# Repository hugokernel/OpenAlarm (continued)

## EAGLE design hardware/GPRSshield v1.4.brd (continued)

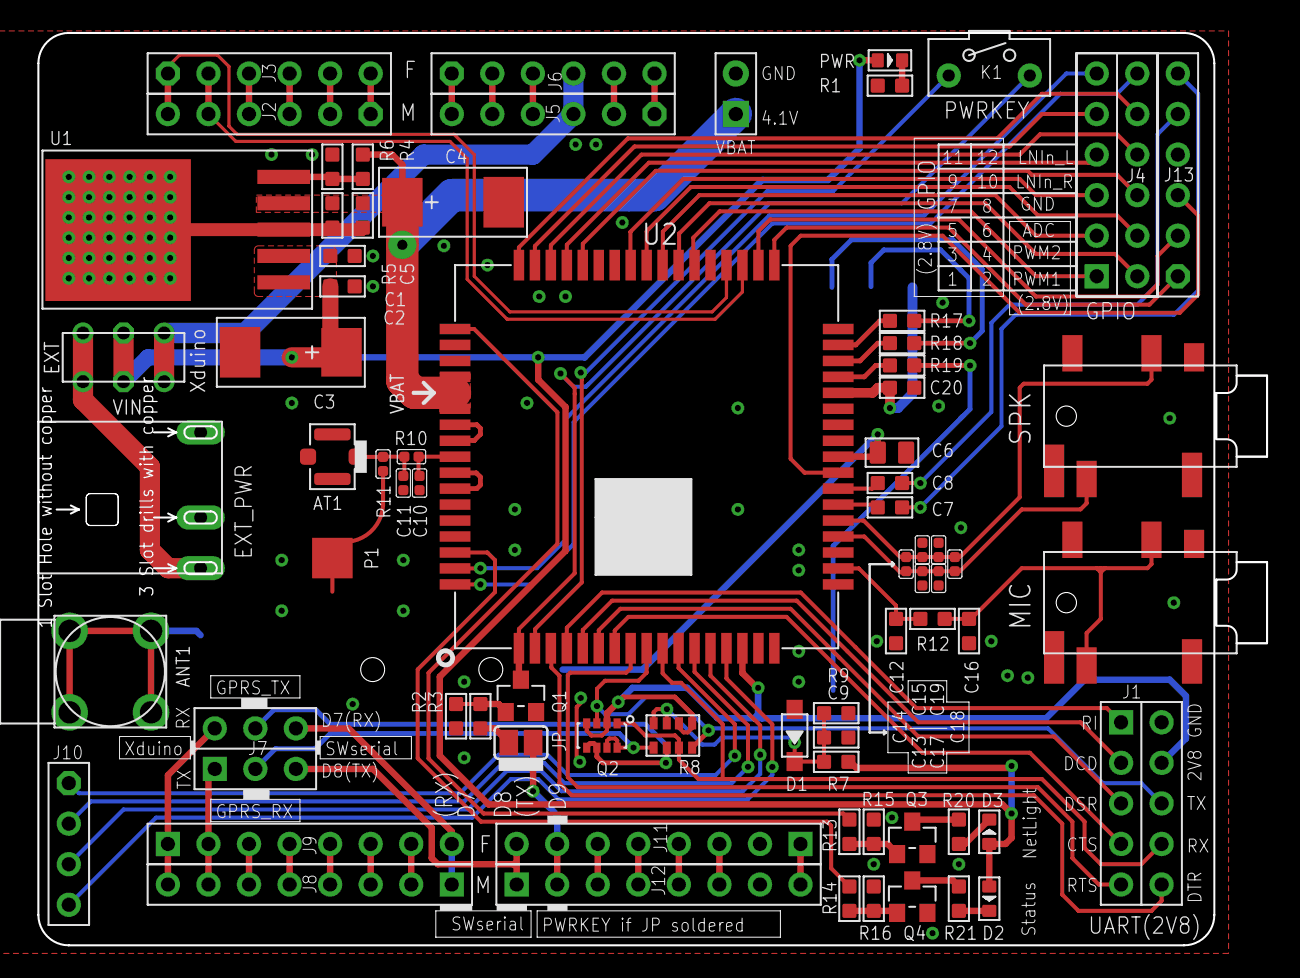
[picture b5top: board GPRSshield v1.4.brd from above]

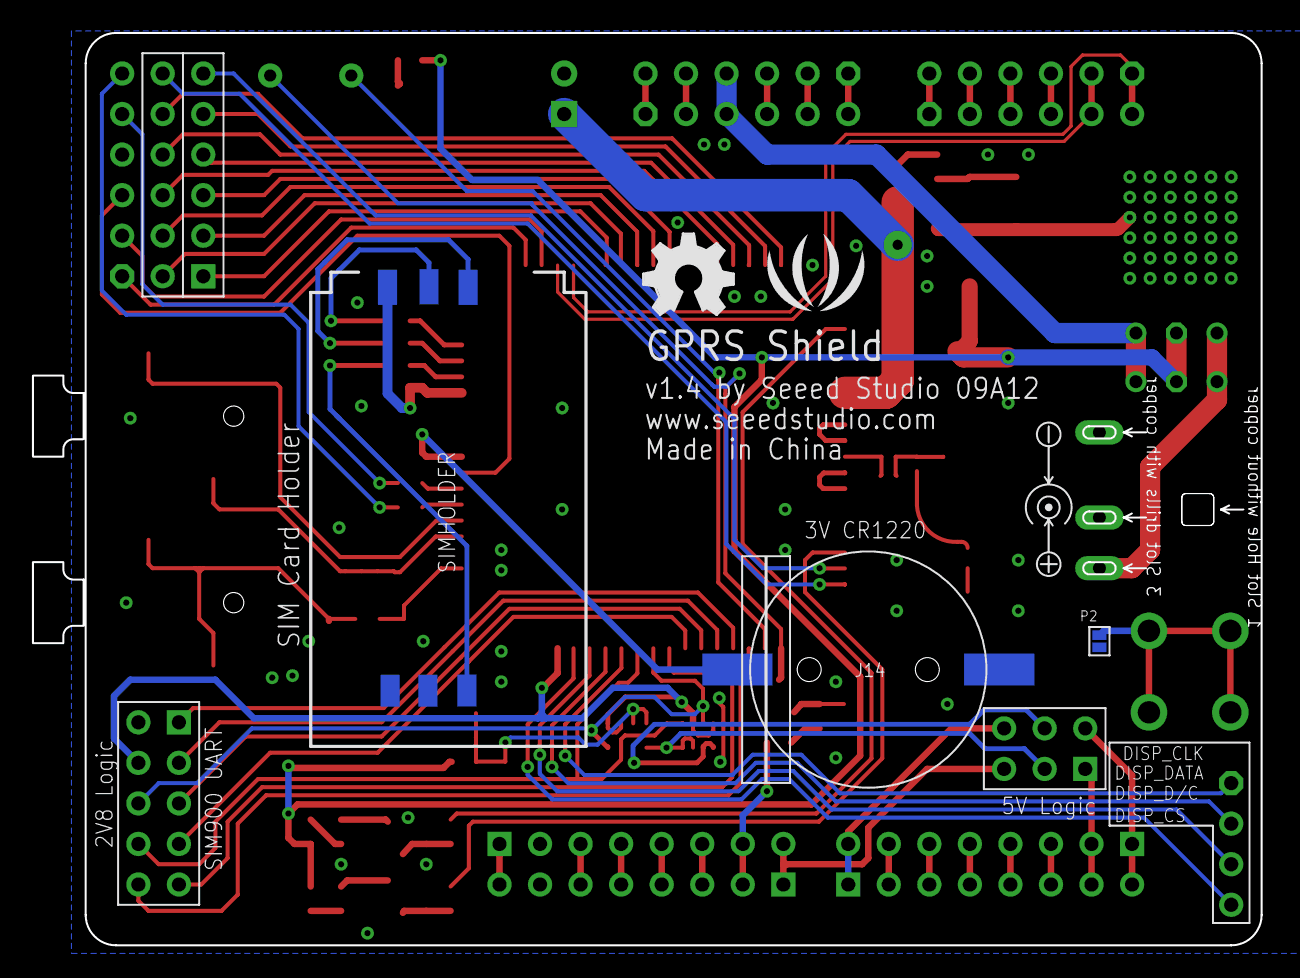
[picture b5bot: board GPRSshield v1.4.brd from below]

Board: 2 copper layers, 77.0 x 57.1 mm, 79 parts (6 on the bottom side), 94 nets.

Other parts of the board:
LOGO1: LOGO-SEEEDSTUDIO-SILK; LOGO_SILK
LOGO2: LOGO-OSHW-FILLX0200-NT; OSHW_FILLX200_NOTEXT

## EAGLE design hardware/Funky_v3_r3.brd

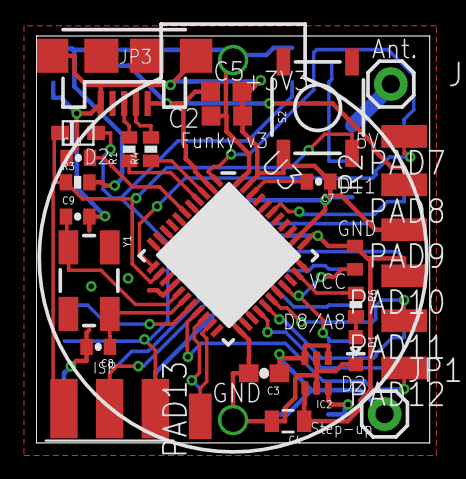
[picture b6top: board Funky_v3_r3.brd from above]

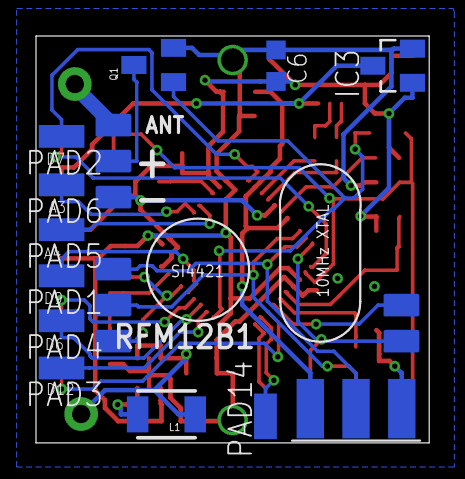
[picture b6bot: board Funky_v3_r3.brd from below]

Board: 2 copper layers, 21.8 x 22.6 mm, 43 parts (12 on the bottom side), 35 nets.

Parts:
BAT2: BATTCOM_20MM_PTH
C2: 100nF; C0603K
C3: 1µ; 0603-CAP
C4: 10µ; 0805
C5: 1uF; C0603K
C6: 1u; C0603K
C7: 100nF; 0402-CAP
C8, C9: 22pF; 0402-CAP
C10: 1uF; 0402-CAP
D1: Green; LED-0603
D2: SOD-323F
IC2: LTC3525; SC70
IC3: MCP1703CB; SOT23
JP1, JP2: M01PTH; 1X01
JP3: USB-MICROB
L1: 10 µH; 1210
PAD1, PAD2, PAD3, PAD4, PAD5, PAD6, PAD7, PAD8, PAD9, PAD10, PAD11, PAD12, PAD13, PAD14: SMD1,27-2,54
Q1: P-MOSFET; SOT23
R1, R4: 22; 0402-RES
R2: 100K; R0402
R3: 10K; 0402-RES
R6: 330; 0402-RES
RFM12B1: RFM12B_MINPADS; RFM12B-MINPADS
S2: !RESET; TACTILE_SWITCH_SMD
U3: ATMEGA32U4; QFN-44-NOPAD
U$2: AVR-ISP-6-EDGE; 6PAD_ISP
Y1: 8MHz; CRYSTAL-SMD-5X3

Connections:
A3: PAD6.1, U3.39
A4: PAD5.1, U3.40
AREF: C7.2, U3.42
D2: PAD12.1, U3.19
D3: RFM12B1.IRQ, U3.18
D4: D2.A, Q1.1, U3.25
D6: PAD4.1, U3.27
D7: PAD2.1, U3.1
D8: PAD11.1, U3.28
D9: PAD1.1, U3.29
D10: R2.1, RFM12B1.SEL, U3.30
D11: PAD7.1, U3.12
D12: PAD3.1, U3.26
D13: R6.1, U3.32
D+: JP3.D+, R1.2
D-: JP3.D-, R4.2
GND: BAT2.2, C2.2, C3.2, C4.2, C5.2, C6.2, C7.1, C8.2, C9.2, C10.1, D1.C, IC2.2, IC2.5, IC3.1, JP3.GND, JP3.MT1, JP3.MT2, PAD9.1, RFM12B1.GND, S2.1, U3.5, U3.15, U3.23, U3.33, U3.35, U3.43, U$2.GND
MISO: RFM12B1.SDO, U3.11, U$2.MISO
MOSI: RFM12B1.SDI, U3.10, U$2.MOSI
unnamed: C9.1, U3.16, Y1.1
unnamed: R1.1, U3.4
unnamed: JP2.1, RFM12B1.ANT
unnamed: C8.1, U3.17, Y1.3
unnamed: C10.2, U3.6
unnamed: D1.A, R6.2
unnamed: R4.1, U3.3
unnamed: Q1.3, RFM12B1.VDD
unnamed: IC2.6, L1.2
RESET: D2.C, R3.1, S2.3, U3.13, U$2.RST
RXI: PAD14.1, U3.20
SCK: RFM12B1.SCK, U3.9, U$2.SCK
TXO: PAD13.1, U3.21
VBUS: C5.1, IC3.3, JP3.VBUS, PAD8.1, U3.2, U3.7, U$2.VCC
VCC: BAT2.1, C2.1, C4.1, C6.1, IC2.4, IC3.2, PAD10.1, Q1.2, R2.2, R3.2, U3.14, U3.24, U3.34, U3.44
VIN: C3.1, IC2.1, IC2.3, JP1.1, L1.1

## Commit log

2014-01-17 Doc + Funky v3
2015-06-10 Node version 1.0.0
2015-08-03 Hardware update
    Node 1.0.0, export and node shield
2015-08-03 Documentation uploaded
2015-08-03 Gitignore update
2015-08-03 Software
2015-08-09 Before resize
2015-08-15 Documentation
2015-08-15 Node Shield
2015-08-15 New node
2015-08-21 Node
    Avancement
2015-08-24 Doc
    Added Max1555 data sheet
2015-08-24 Node
2015-08-27 Max1555 backup
    Finally, design with max1555 is a bad idea !
2015-08-28 Node + Proto Shield + Lipo Shield
2015-08-28 Node + 2 Proto Shield + Lipo Shield
2015-09-24 Code !
2015-09-24 Node 1.5.0
2015-10-06 Hardware modification
2015-10-06 Python development
2015-10-06 OpenAlarm Node firmware
2015-10-22 Misc
2015-12-05 PDF file
2015-12-05 Clean !
2015-12-08 Remove extEEPROM
2015-12-08 RSSI Test
2015-12-08 Clean extEEPROM
2015-12-08 Bug correction with remote command
2015-12-08 RF init
